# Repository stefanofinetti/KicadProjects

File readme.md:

# Kicad Projects File

This is a repository of my Kicad projects. Not everyone is working, I will list here the ones that I used and that I already sent to JLCPCB for printing.

* FCU_Mainboard_V3: a complete mainboard for FCU and both EFIS panels for Fenix A319/320/321. It is based on ATMega2560 chip with CH340G USB-To-Serial converter. All the components are SMD except for pin headers and the power selector switch to change between USB power and Bootloading using another card as Programmer. It works with Elral/Gagaru custom device firmare for Mobiflight since it has 6 SSD1306 OLED displays
* RMP_V2: a Radio Management Panel using ATMega2560 using two small OLED (0.96"), basically half the height of an SSD1306 OLED. It has a 9548APW chip and a separate 5V line for backlighting. It is meant to be mounted directly behind a 3d printed panel and provides backlighting to buttons and writings.
* LTS_Spooler: not Mobiflight related, it's the circuit board usable inside the fantastic LTS_Spooler project you can find here: https://makerworld.com/en/models/448008#profileId-354782

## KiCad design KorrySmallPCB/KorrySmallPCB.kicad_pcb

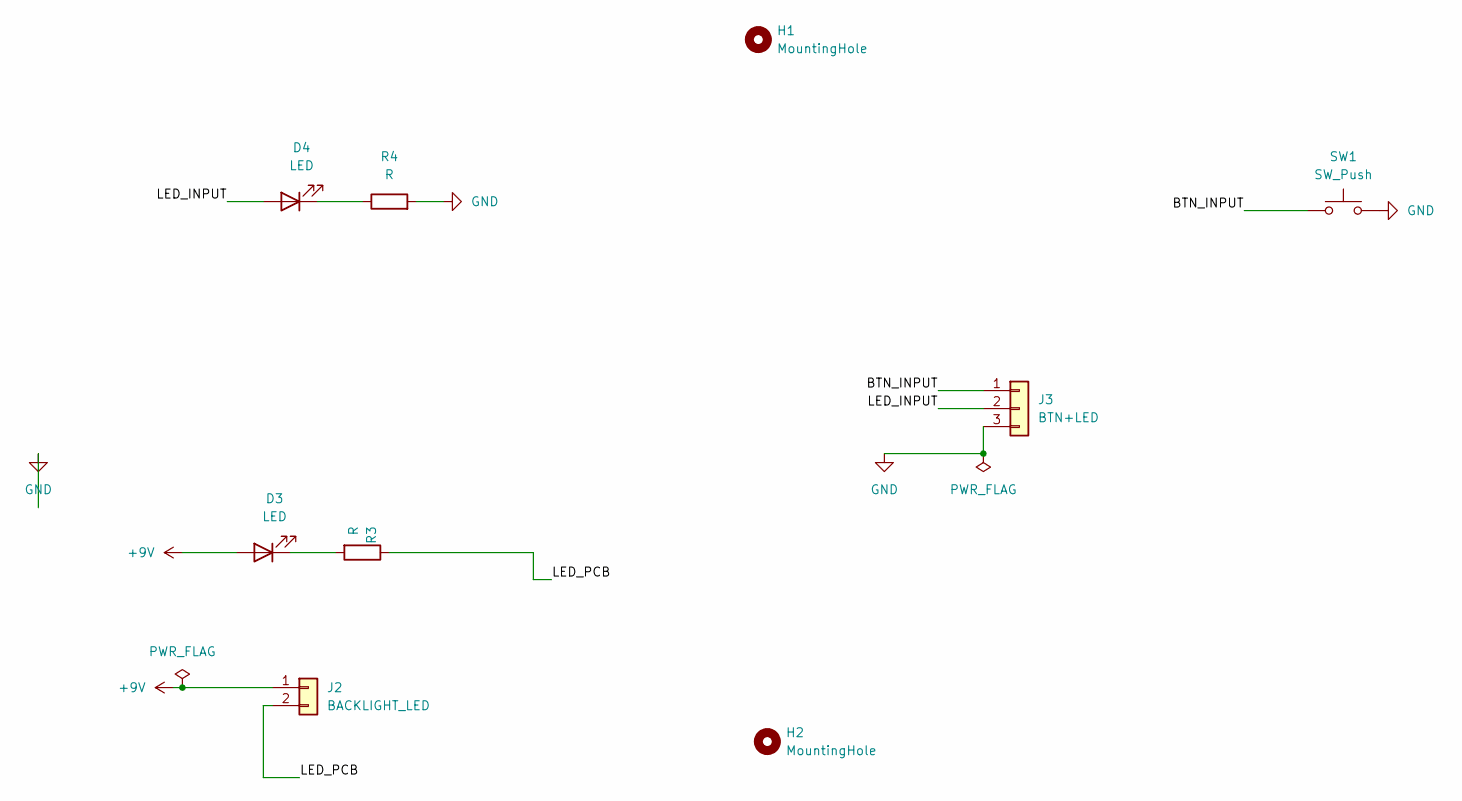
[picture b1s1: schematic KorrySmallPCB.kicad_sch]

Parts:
D3, D4: LED; LED_D3.0mm
H1, H2: MountingHole; MountingHole_2.2mm_M2_DIN965_Pad_TopBottom
J2: BACKLIGHT_LED; JST_EH_B2B-EH-A_1x02_P2.50mm_Vertical
J3: BTN+LED; JST_EH_B3B-EH-A_1x03_P2.50mm_Vertical
R3, R4: R; R_Axial_DIN0207_L6.3mm_D2.5mm_P7.62mm_Horizontal
SW1: SW_Push; SW_PUSH_1P1T_6x3.5mm_H4.3_APEM_MJTP1243

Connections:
+9V: D3.2 (A), J2.1
/BTN_INPUT: J3.1, SW1.1
/LED_INPUT: D4.2 (A), J3.2
/LED_PCB: J2.2, R3.1
GND: J3.3, R4.2, SW1.2
unnamed: D3.1 (K), R3.2
unnamed: D4.1 (K), R4.1

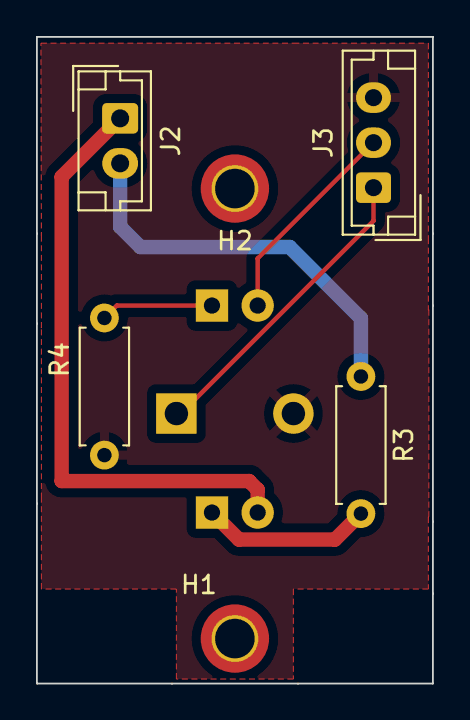
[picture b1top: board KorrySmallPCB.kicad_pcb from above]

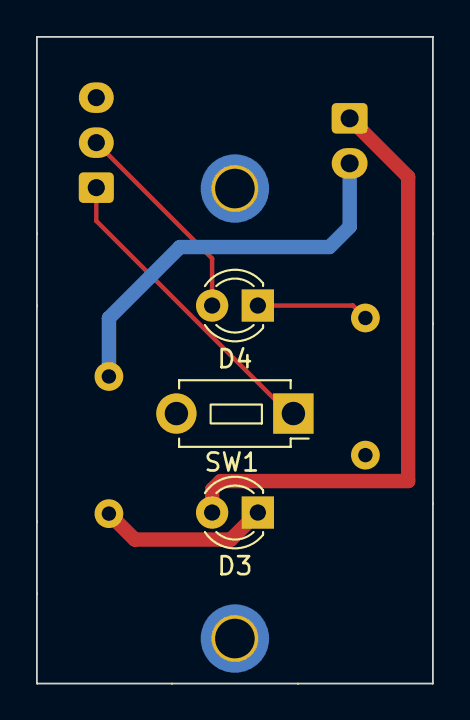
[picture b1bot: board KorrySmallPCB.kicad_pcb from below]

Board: 2 copper layers, 22.0 x 35.9 mm, 9 parts (3 on the bottom side), 7 nets.

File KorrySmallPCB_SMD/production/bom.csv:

Designator,Footprint,Quantity,Value,LCSC Part #
"DG-1, DW-1",1206,2,LED,
"H1, H2",MountingHole_2.5mm_Pad_TopBottom,2,MountingHole,
J1,PinHeader_1x03_P2.54mm_Vertical,1,BTN+LED,
J2,PinHeader_1x02_P2.54mm_Vertical,1,BK_LED,
"RG-1, RW-1",1206,2,R,
SW1,SW_PUSH_1P1T_6x3.5mm_H4.3_APEM_MJTP1243,1,SW,C4364985

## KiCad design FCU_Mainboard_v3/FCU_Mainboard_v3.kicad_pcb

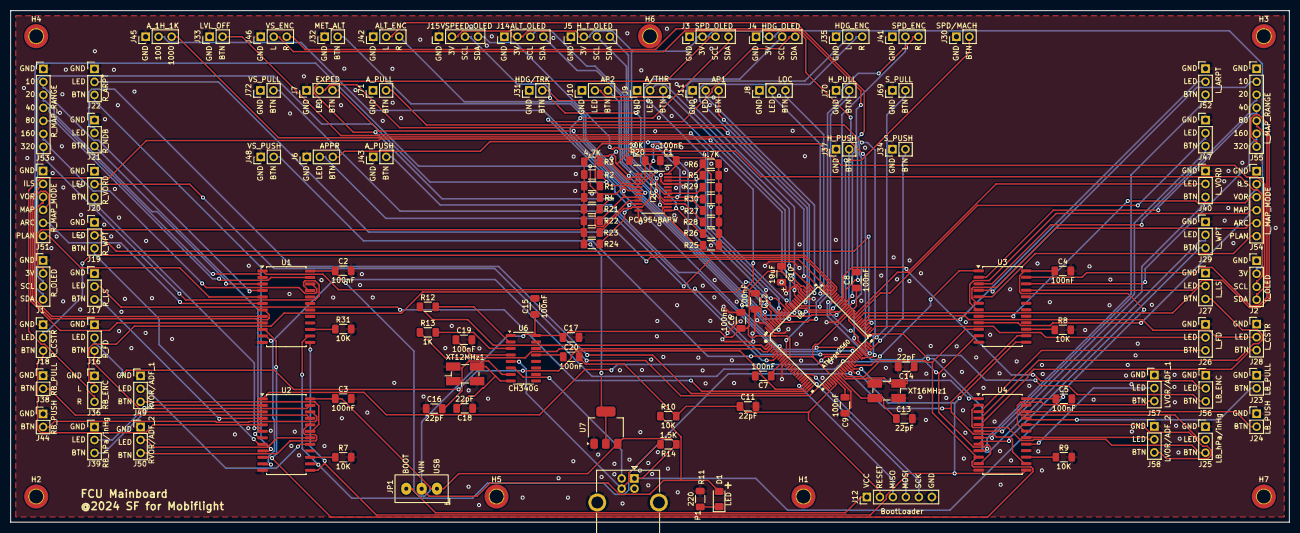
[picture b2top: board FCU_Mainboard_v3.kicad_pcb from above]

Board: 2 copper layers, 250.0 x 100.0 mm, 127 parts (0 on the bottom side), 156 nets.

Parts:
C1, C2, C3, C4, C5, C6, C7, C8, C9, C12, C15, C17, C19, C20: 100nF; C_1206_3216Metric_Pad1.33x1.80mm_HandSolder
C10: 10uF; C_1206_3216Metric_Pad1.33x1.80mm_HandSolder
C11, C13, C14, C16, C18: 22pF; C_1206_3216Metric_Pad1.33x1.80mm_HandSolder
D1: LED; LED_1206_3216Metric_Pad1.42x1.75mm_HandSolder
H1, H2, H3, H4, H5, H6, H7: MountingHole; MountingHole_2.7mm_M2.5_DIN965_Pad_TopBottom
I2C_1: PCA9548APW; SOP65P640X120-24N
J1: R_OLED; PinHeader_1x04_P2.54mm_Vertical
J2: L_OLED; PinHeader_1x04_P2.54mm_Vertical
J3: SPD_OLED; PinHeader_1x04_P2.54mm_Vertical
J4: HDG_OLED; PinHeader_1x04_P2.54mm_Vertical
J5: H_T_OLED; PinHeader_1x04_P2.54mm_Vertical
J6: APPR; PinHeader_1x03_P2.54mm_Vertical
J7: EXPED; PinHeader_1x03_P2.54mm_Vertical
J8: LOC; PinHeader_1x03_P2.54mm_Vertical
J9: A/THR; PinHeader_1x03_P2.54mm_Vertical
J10: AP2; PinHeader_1x03_P2.54mm_Vertical
J11: AP1; PinHeader_1x03_P2.54mm_Vertical
J12: BootLoader; PinHeader_1x06_P2.54mm_Vertical
J14: ALT_OLED; PinHeader_1x04_P2.54mm_Vertical
J15: VSPEED_OLED; PinHeader_1x04_P2.54mm_Vertical
J16: R_FD; PinHeader_1x03_P2.54mm_Vertical
J17: R_LS; PinHeader_1x03_P2.54mm_Vertical
J18: R_CSTR; PinHeader_1x03_P2.54mm_Vertical
J19: R_WPT; PinHeader_1x03_P2.54mm_Vertical
J20: R_VORD; PinHeader_1x03_P2.54mm_Vertical
J21: R_NDB; PinHeader_1x03_P2.54mm_Vertical
J22: R_ARPT; PinHeader_1x03_P2.54mm_Vertical
J23: LB_PULL; PinHeader_1x02_P2.54mm_Vertical
J24: LB_PUSH; PinHeader_1x02_P2.54mm_Vertical
J25: LB_hPa/inHg; PinHeader_1x03_P2.54mm_Vertical
J26: L_FD; PinHeader_1x03_P2.54mm_Vertical
J27: L_LS; PinHeader_1x03_P2.54mm_Vertical
J28: L_CSTR; PinHeader_1x03_P2.54mm_Vertical
J29: L_WPT; PinHeader_1x03_P2.54mm_Vertical
J30: SPD/MACH; PinHeader_1x02_P2.54mm_Vertical
J31: HDG/TRK; PinHeader_1x02_P2.54mm_Vertical
J32: MET_ALT; PinHeader_1x02_P2.54mm_Vertical
J33: LVL_OFF; PinHeader_1x02_P2.54mm_Vertical
J34: S_PUSH; PinHeader_1x02_P2.54mm_Vertical
J35: HDG_ENC; PinHeader_1x03_P2.54mm_Vertical
J36: RB_ENC; PinHeader_1x03_P2.54mm_Vertical
J37: H_PUSH; PinHeader_1x02_P2.54mm_Vertical
J38: RB_PULL; PinHeader_1x02_P2.54mm_Vertical
J39: RB_hPa/inHg; PinHeader_1x03_P2.54mm_Vertical
J40: L_VORD; PinHeader_1x03_P2.54mm_Vertical
J41: SPD_ENC; PinHeader_1x03_P2.54mm_Vertical
J42: ALT_ENC; PinHeader_1x03_P2.54mm_Vertical
J43: A_PUSH; PinHeader_1x02_P2.54mm_Vertical
J44: RB_PUSH; PinHeader_1x02_P2.54mm_Vertical
J45: A_1H_1K; PinHeader_1x03_P2.54mm_Vertical
J46: VS_ENC; PinHeader_1x03_P2.54mm_Vertical
J47: L_NDB; PinHeader_1x03_P2.54mm_Vertical
J48: VS_PUSH; PinHeader_1x02_P2.54mm_Vertical
J49: RVOR/ADF_1; PinHeader_1x03_P2.54mm_Vertical
J50: RVOR/ADF_2; PinHeader_1x03_P2.54mm_Vertical
J51: R_MAP_MODE; PinHeader_1x06_P2.54mm_Vertical
J52: L_ARPT; PinHeader_1x03_P2.54mm_Vertical
J53: R_MAP_RANGE; PinHeader_1x07_P2.54mm_Vertical
J54: L_MAP_MODE; PinHeader_1x06_P2.54mm_Vertical
J55: L_MAP_RANGE; PinHeader_1x07_P2.54mm_Vertical
J56: LB_ENC; PinHeader_1x03_P2.54mm_Vertical
J57: LVOR/ADF_1; PinHeader_1x03_P2.54mm_Vertical
J58: LVOR/ADF_2; PinHeader_1x03_P2.54mm_Vertical
J69: S_PULL; PinHeader_1x02_P2.54mm_Vertical
J70: H_PULL; PinHeader_1x02_P2.54mm_Vertical
J71: A_PULL; PinHeader_1x02_P2.54mm_Vertical
J72: VS_PULL; PinHeader_1x02_P2.54mm_Vertical
JP1: Power Selector; Slide_Switch_SPDT_P3mm_10x5x10mm
P1: USB_C_Plug_USB2.0; USB_B_OST_USB-B1HSxx_Horizontal
R1, R2, R3, R4, R5, R6, R21, R22, R23, R24, R25, R26, R27, R28, R29, R30: 4.7K; R_1206_3216Metric_Pad1.30x1.75mm_HandSolder
R7, R8, R9, R10, R20, R31: 10K; R_1206_3216Metric_Pad1.30x1.75mm_HandSolder
R11: 220; R_1206_3216Metric_Pad1.30x1.75mm_HandSolder
R12, R13: 1K; R_1206_3216Metric_Pad1.30x1.75mm_HandSolder
R14: 1.5K; R_1206_3216Metric_Pad1.30x1.75mm_HandSolder
U1, U2, U3, U4: CD74HC4067M; SOIC-24W_7.5x15.4mm_P1.27mm
U5: ATMega2560; TQFP100-0.5-14X14MM
U6: CH340G; SOIC-16_3.9x9.9mm_P1.27mm
U7: AMS1117-3.3; SOT-223-3_TabPin2
XT12MHz1: 12MHz; Crystal_SMD_EuroQuartz_MJ-4Pin_5.0x3.2mm_HandSoldering
XT16MHz1: 16MHz; Crystal_SMD_EuroQuartz_MJ-4Pin_5.0x3.2mm_HandSoldering

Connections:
+3V3: C1.1, I2C_1.24 (VCC), J1.2, J2.2, J3.2, J4.2, J5.2, J14.2, J15.2, R1.1, R2.2, R3.1, R4.1, R5.2, R6.1, R20.1, R21.1, R22.1, R23.1, R24.1, R25.1, R26.1, R27.1, R28.1, R29.1, R30.1, U7.2 (VO)
+5V: C2.1, C3.1, C4.1, C5.1, JP1.1 (A), P1.1 (VBUS), R14.1, U1.24 (VCC), U2.24 (VCC), U3.24 (VCC), U4.24 (VCC), U7.3 (VI)
/EFIS_LEFT/ADF 1: J57.3, U4.19 (I12)
/EFIS_LEFT/ADF 2: J58.3, U4.20 (I11)
/EFIS_LEFT/ARC: J54.5, U3.6 (I3)
/EFIS_LEFT/ARPT_BTN: J52.3, U4.9 (I0)
/EFIS_LEFT/BARO_PULL: J23.2, U4.21 (I10)
/EFIS_LEFT/BARO_PUSH: J24.2, U4.22 (I9)
/EFIS_LEFT/BARO_hPa: J25.2, U4.23 (I8)
/EFIS_LEFT/BARO_inHg: J25.3, U4.2 (I7)
/EFIS_LEFT/CSTR_BTN: J28.3, U4.5 (I4)
/EFIS_LEFT/FD_BTN: J26.3, U4.3 (I6)
/EFIS_LEFT/ILS: J54.2, U3.9 (I0)
/EFIS_LEFT/LS_BTN: J27.3, U4.4 (I5)
/EFIS_LEFT/MAP: J54.4, U3.7 (I2)
/EFIS_LEFT/NDB_BTN: J47.3, U4.7 (I2)
/EFIS_LEFT/PLAN: J54.6, U3.5 (I4)
/EFIS_LEFT/R10: J55.2, U3.4 (I5)
/EFIS_LEFT/R20: J55.3, U3.3 (I6)
/EFIS_LEFT/R40: J55.4, U3.2 (I7)
/EFIS_LEFT/R80: J55.5, U3.23 (I8)
/EFIS_LEFT/R160: J55.6, U3.22 (I9)
/EFIS_LEFT/R320: J55.7, U3.21 (I10)
/EFIS_LEFT/VOR: J54.3, U3.8 (I1)
/EFIS_LEFT/VOR 1: J57.2, U4.17 (I14)
/EFIS_LEFT/VOR 2: J58.2, U4.18 (I13)
/EFIS_LEFT/VORD_BTN: J40.3, U4.6 (I3)
/EFIS_LEFT/WPT_BTN: J29.3, U4.8 (I1)
/EFIS_RIGHT/ADF 1: J49.3, U2.19 (I12)
/EFIS_RIGHT/ADF 2: J50.3, U2.20 (I11)
/EFIS_RIGHT/ARC: J51.5, U1.6 (I3)
/EFIS_RIGHT/ARPT_BTN: J22.3, U2.9 (I0)
/EFIS_RIGHT/BARO_PULL: J38.2, U2.21 (I10)
/EFIS_RIGHT/BARO_PUSH: J44.2, U2.22 (I9)
/EFIS_RIGHT/BARO_hPa: J39.2, U2.23 (I8)
/EFIS_RIGHT/BARO_inHg: J39.3, U2.2 (I7)
/EFIS_RIGHT/CSTR_BTN: J18.3, U2.5 (I4)
/EFIS_RIGHT/FD_BTN: J16.3, U2.3 (I6)
/EFIS_RIGHT/ILS: J51.2, U1.9 (I0)
/EFIS_RIGHT/LS_BTN: J17.3, U2.4 (I5)
/EFIS_RIGHT/MAP: J51.4, U1.7 (I2)
/EFIS_RIGHT/NDB_BTN: J21.3, U2.7 (I2)
/EFIS_RIGHT/PLAN: J51.6, U1.5 (I4)
/EFIS_RIGHT/R10: J53.2, U1.4 (I5)
/EFIS_RIGHT/R20: J53.3, U1.3 (I6)
/EFIS_RIGHT/R40: J53.4, U1.2 (I7)
/EFIS_RIGHT/R80: J53.5, U1.23 (I8)
/EFIS_RIGHT/R160: J53.6, U1.22 (I9)
/EFIS_RIGHT/R320: J53.7, U1.21 (I10)
/EFIS_RIGHT/VOR: J51.3, U1.8 (I1)
/EFIS_RIGHT/VOR 1: J49.2, U2.17 (I14)
/EFIS_RIGHT/VOR 2: J50.2, U2.18 (I13)
/EFIS_RIGHT/VORD_BTN: J20.3, U2.6 (I3)
/EFIS_RIGHT/WPT_BTN: J19.3, U2.8 (I1)
/OLEDs/ALT_SCL: I2C_1.16 (SC5), J14.3, R27.2
/OLEDs/ALT_SDA: I2C_1.15 (SD5), J14.4, R28.2
/OLEDs/HDG_SCL: I2C_1.11 (SC3), J4.3, R23.2
/OLEDs/HDG_SDA: I2C_1.10 (SD3), J4.4, R24.2
/OLEDs/HDG/TRK_SCL: I2C_1.14 (SC4), J5.3, R25.2
/OLEDs/HDG/TRK_SDA: I2C_1.13 (SD4), J5.4, R26.2
/OLEDs/L_EFIS_SCL: I2C_1.7 (SC1), J2.3, R1.2
/OLEDs/L_EFIS_SDA: I2C_1.4 (SD0), J2.4, R3.2
/OLEDs/R_EFIS_SCL: I2C_1.5 (SC0), J1.3, R2.1
/OLEDs/R_EFIS_SDA: I2C_1.6 (SD1), J1.4, R4.2
/OLEDs/SPD_SCL: I2C_1.9 (SC2), J3.3, R21.2
/OLEDs/SPD_SDA: I2C_1.8 (SD2), J3.4, R22.2
/OLEDs/VSPEED_SCL: I2C_1.18 (SC6), J15.3, R29.2
/OLEDs/VSPEED_SDA: I2C_1.17 (SD6), J15.4, R30.2
ALT_100: J45.2, U5.45 (PD2)
ALT_1000: J45.3, U5.46 (PD3)
ALT_LEFT: J42.2, U5.63 (PJ0)
ALT_PULL: J71.2, U5.44 (PD1)
ALT_PUSH: J43.2, U5.43 (PD0)
ALT_RIGHT: J42.3, U5.64 (PJ1)
AP1_BTN: J11.3, U5.9 (PE7)
AP1_LED: J10.2, U5.78 (PA0)
AP2_BTN: J10.3, U5.97 (PF0)
AP2_LED: J11.2, U5.77 (PA1)
APPR_BTN: J6.3, U5.96 (PF1)
APPR_LED: J6.2, U5.75 (PA3)
A/THR_BTN: J9.3, U5.8 (PE6)
A/THR_LED: J9.2, U5.76 (PA2)
EXPED_BTN: J7.3, U5.95 (PF2)
EXPED_LED: J7.2, U5.74 (PA4)
GND: C1.2, C2.2, C3.2, C4.2, C5.2, C6.2, C7.2, C8.2, C9.2, C10.2, C11.2, C12.2, C13.2, C14.2, C15.2, C16.1, C17.2, C18.1, C19.2, I2C_1.1 (A0), I2C_1.2 (A1), I2C_1.12 (GND), I2C_1.21 (A2), J1.1, J2.1, J3.1, J4.1, J5.1, J6.1, J7.1, J8.1, J9.1, J10.1, J11.1, J12.6, J14.1, J15.1, J16.1, J17.1, J18.1, J19.1, J20.1, J21.1, J22.1, J23.1, J24.1, J25.1, J26.1, J27.1, J28.1, J29.1, J30.1, J31.1, J32.1, J33.1, J34.1, J35.1, J36.1, J37.1, J38.1, J39.1, J40.1, J41.1, J42.1, J43.1, J44.1, J45.1, J46.1, J47.1, J48.1, J49.1, J50.1, J51.1, J52.1, J53.1, J54.1, J55.1, J56.1, J57.1, J58.1, J69.1, J70.1, J71.1, J72.1, P1.4 (GND), P1.5 (Shield), R7.2, R8.2, R9.2, R11.1, R31.2, U1.12 (GND), U2.12 (GND), U3.12 (GND), U4.12 (GND), U5.11 (GND), U5.32 (GND), U5.62 (GND), U5.81 (GND), U5.99 (GND), U6.1 (GND), U7.1 (GND), XT12MHz1.2, XT12MHz1.4, XT16MHz1.2, XT16MHz1.4
HDG_LEFT: J35.2, U5.83 (PK6)
HDG_PULL: J70.2, U5.48 (PD5)
HDG_PUSH: J37.2, U5.47 (PD4)
HDG_RIGHT: J35.3, U5.82 (PK7)
HDG/TRK_BTN: J31.2, U5.93 (PF4)
LOC_BTN: J8.3, U5.94 (PF3)
LOC_LED: J8.2, U5.73 (PA5)
LVL_OFF_BTN: J33.2, U5.92 (PF5)
L_EFIS_ARPT_LED: J52.2, U5.54 (PC1)
L_EFIS_BARO_LEFT: J56.2, U5.67 (PJ4)
L_EFIS_BARO_RIGHT: J56.3, U5.68 (PJ5)
L_EFIS_CSTR_LED: J28.2, U5.55 (PC2)
L_EFIS_FD_LED: J26.2, U5.56 (PC3)
L_EFIS_LS_LED: J27.2, U5.57 (PC4)
L_EFIS_NDB_LED: J47.2, U5.58 (PC5)
L_EFIS_VORD_LED: J40.2, U5.59 (PC6)
L_EFIS_WPT_LED: J29.2, U5.60 (PC7)
METRIC_ALT_BTN: J32.2, U5.91 (PF6)
MISO: J12.3, U5.22 (PB3)
MOSI: J12.4, U5.21 (PB2)
MP_S0: U1.10 (S0), U2.10 (S0), U3.10 (S0), U4.10 (S0), U5.35 (PL0)
MP_S1: U1.11 (S1), U2.11 (S1), U3.11 (S1), U4.11 (S1), U5.36 (PL1)
MP_S2: U1.14 (S2), U2.14 (S2), U3.14 (S2), U4.14 (S2), U5.37 (PL2)
MP_S3: U1.13 (S3), U2.13 (S3), U3.13 (S3), U4.13 (S3), U5.38 (PL3)
unnamed: D1.1 (K), R11.2
unnamed: I2C_1.3 (~RESET), R20.2
unnamed: R31.1, U1.15 (~E)
unnamed: R7.1, U2.15 (~E)
unnamed: R8.1, U3.15 (~E)
unnamed: R9.1, U4.15 (~E)
unnamed: C12.1, U5.98 (AREF)
unnamed: C14.1, U5.34 (XTAL1), XT16MHz1.1
unnamed: C13.1, U5.33 (XTAL2), XT16MHz1.3
unnamed: R13.2, U6.3 (RXD)
unnamed: R12.2, U6.2 (TXD)
unnamed: C19.1, U6.4 (V3)
unnamed: C16.2, U6.7 (XI), XT12MHz1.1
unnamed: C18.2, U6.8 (XO), XT12MHz1.3
unnamed: C20.1, U6.13 (~DTR)
RESET: C11.1, C20.2, J12.2, R10.2, U5.30 (~RESET)
RXD: R12.1, U5.2 (PE0)
R_EFIS_ARPT_LED: J22.2, U5.72 (PA6)
R_EFIS_BARO_LEFT: J36.2, U5.87 (PK2)
R_EFIS_BARO_RIGHT: J36.3, U5.86 (PK3)
R_EFIS_CSTR_LED: J18.2, U5.71 (PA7)
R_EFIS_FD_LED: J16.2, U5.23 (PB4)
R_EFIS_LS_LED: J17.2, U5.24 (PB5)
R_EFIS_NDB_LED: J21.2, U5.25 (PB6)
R_EFIS_VORD_LED: J20.2, U5.26 (PB7)
R_EFIS_WPT_LED: J19.2, U5.53 (PC0)
SCK: J12.5, U5.20 (PB1)
SCL: I2C_1.22 (SCL), R5.1, U5.89 (PK0)
SDA: I2C_1.23 (SDA), R6.2, U5.88 (PK1)
SPD_LEFT: J41.2, U5.85 (PK4)
SPD_PULL: J69.2, U5.50 (PD7)
SPD_PUSH: J34.2, U5.49 (PD6)
SPD_RIGHT: J41.3, U5.84 (PK5)
SPD/MACH_BTN: J30.2, U5.90 (PF7)
TXD: R13.1, U5.3 (PE1)
U1_MP_SIG: U1.1 (COM), U5.42 (PL7)
U2_MP_SIG: U2.1 (COM), U5.41 (PL6)
U3_MP_SIG: U3.1 (COM), U5.40 (PL5)
U4_MP_SIG: U4.1 (COM), U5.39 (PL4)
UD+: P1.3 (D+), R14.2, U6.5 (UD+)
UD-: P1.2 (D-), U6.6 (UD-)
VCC: J12.1, JP1.3 (C)
VIN: C6.1, C7.1, C8.1, C9.1, C10.1, C15.1, C17.1, D1.2 (A), JP1.2 (B), R10.1, U5.10 (VCC), U5.31 (VCC), U5.61 (VCC), U5.80 (VCC), U5.100 (AVCC), U6.16 (VCC)
VSPEED_LEFT: J46.2, U5.65 (PJ2)
VSPEED_PULL: J72.2, U5.7 (PE5)
VSPEED_PUSH: J48.2, U5.6 (PE4)
VSPEED_RIGHT: J46.3, U5.66 (PJ3)

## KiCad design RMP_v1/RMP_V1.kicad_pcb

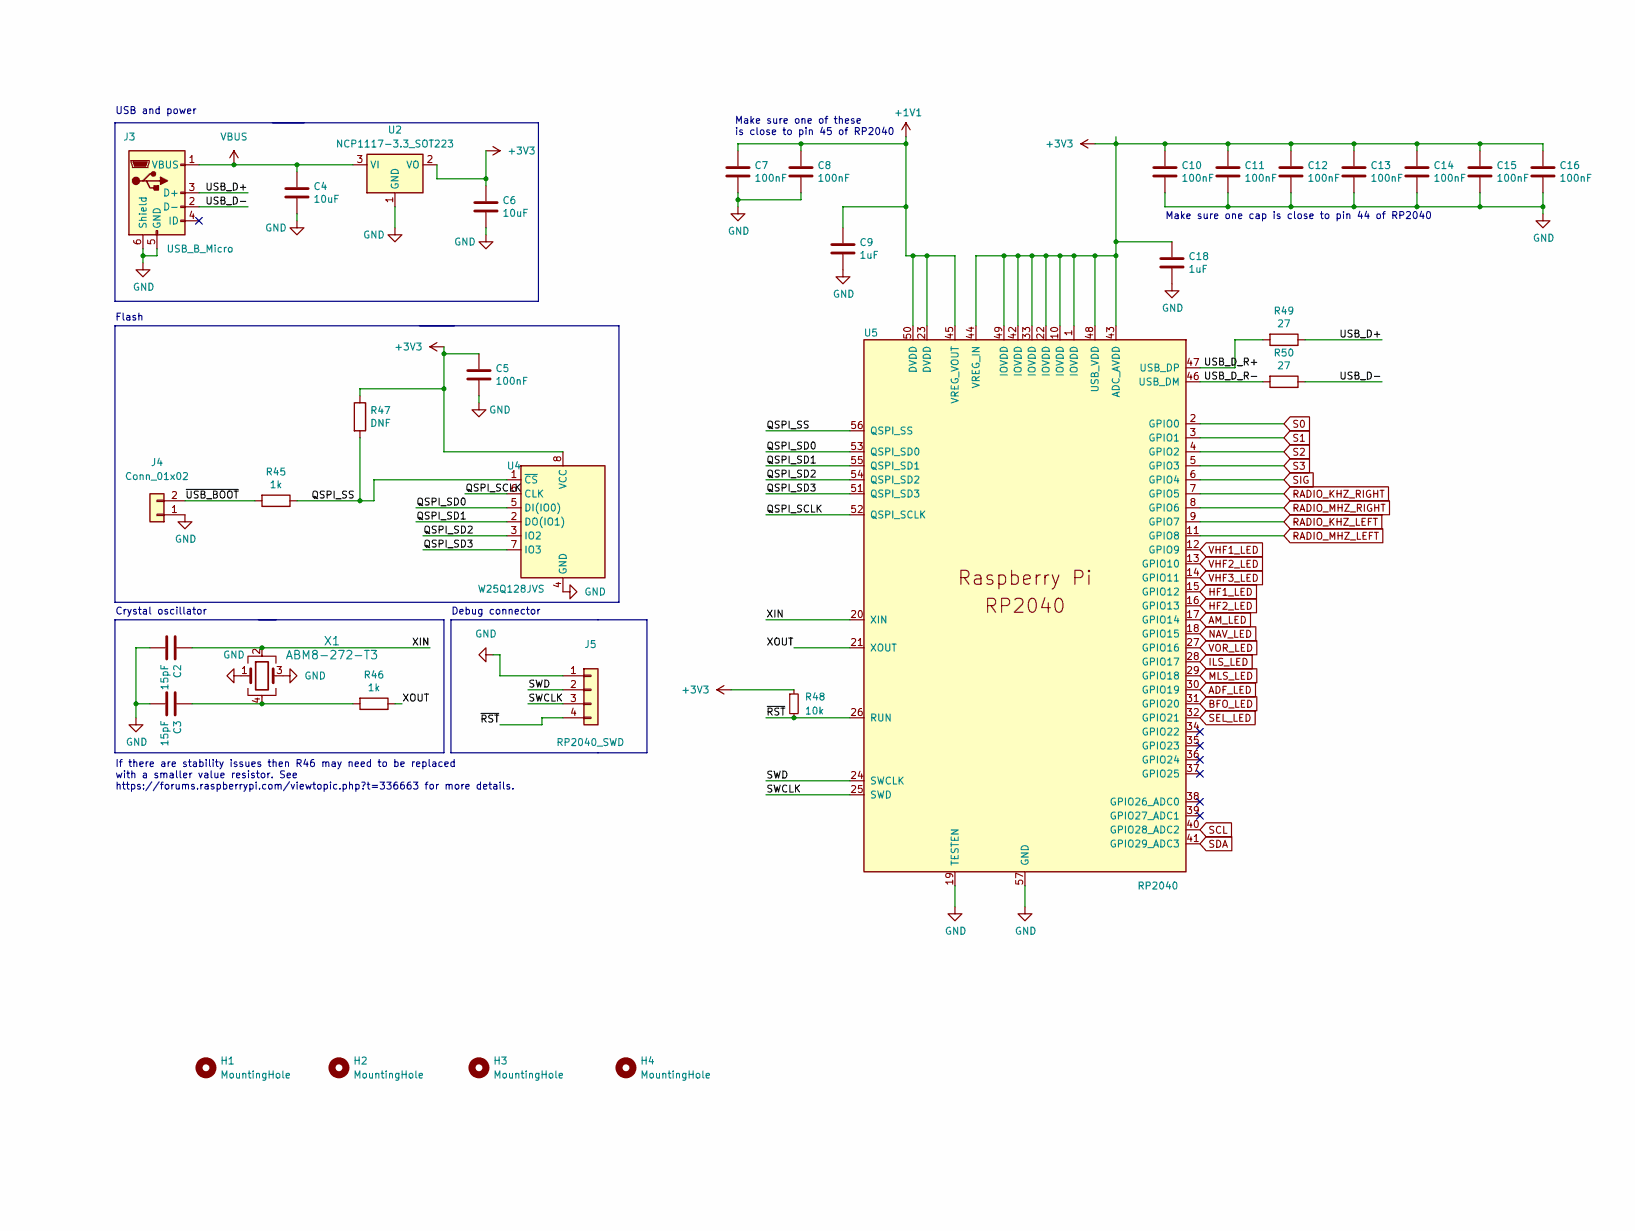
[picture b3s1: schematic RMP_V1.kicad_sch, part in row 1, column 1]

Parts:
C2, C3: 15pF; Perfect_0402; MPN - JLCPCB C32949
C4, C6: 10uF; Perfect_0402; MPN - JLCPCB C52923
C5, C7, C8, C10, C11, C12, C13, C14, C15, C16: 100nF; Perfect_0402; MPN - JLCPCB C52923
C9, C18: 1uF; Perfect_0402; MPN - JLCPCB C52923
H1, H2, H3, H4: MountingHole; MountingHole_3.2mm_M3
J3: USB_B_Micro; USB_B_Mini_Amphenol_UE25BE5510H
J4: Conn_01x02; PinHeader_1x02_P2.54mm_Vertical
J5: RP2040_SWD; PinHeader_1x04_P2.54mm_Vertical
R45, R46: 1k; R_0402_1005Metric; MPN - JLCPCB C11702
R47: DNF; R_0402_1005Metric
R48: 10k; R_0402_1005Metric; MPN - JLCPCB C25744
R49, R50: 27; R_0402_1005Metric; MPN - JLCPCB C25190
U2: NCP1117-3.3_SOT223; SOT-223-3_TabPin2; MPN - JLCPCB C6186
U4: W25Q128JVS; SOIC-8_5.23x5.23mm_P1.27mm; MPN - JLCPCB C97521
U5: RP2040; QFN-56-1EP_7x7mm_P0.4mm_EP3.2x3.2mm; MPN - JLCPCB C2040
X1: ABM8-272-T3; Crystal_SMD_3225-4Pin_3.2x2.5mm; MPN - JLCPCB C9002

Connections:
+1V1: C7.1, C8.1, C9.1, U5.23 (DVDD), U5.45 (VREG_VOUT), U5.50 (DVDD)
+3V3: C5.1, C6.1, C10.1, C11.1, C12.1, C13.1, C14.1, C15.1, C16.1, C18.1, R47.1, R48.1, U2.2 (VO), U4.8 (VCC), U5.1 (IOVDD), U5.10 (IOVDD), U5.22 (IOVDD), U5.33 (IOVDD), U5.42 (IOVDD), U5.43 (ADC_AVDD), U5.44 (VREG_IN), U5.48 (USB_VDD), U5.49 (IOVDD); also elsewhere on the board
/QSPI_SCLK: U4.6 (CLK), U5.52 (QSPI_SCLK)
/QSPI_SD0: U4.5 (DI(IO0)), U5.53 (QSPI_SD0)
/QSPI_SD1: U4.2 (DO(IO1)), U5.55 (QSPI_SD1)
/QSPI_SD2: U4.3 (IO2), U5.54 (QSPI_SD2)
/QSPI_SD3: U4.7 (IO3), U5.51 (QSPI_SD3)
/QSPI_SS: R45.1, R47.2, U4.1 (~CS), U5.56 (QSPI_SS)
/SWCLK: J5.3, U5.25 (SWD)
/SWD: J5.2, U5.24 (SWCLK)
/USB_D+: J3.3 (D+), R49.1
/USB_D-: J3.2 (D-), R50.1
/USB_D_R+: R49.2, U5.47 (USB_DP)
/USB_D_R-: R50.2, U5.46 (USB_DM)
/XIN: C2.1, U5.20 (XIN), X1.2
/XOUT: R46.1, U5.21 (XOUT)
/~RST: J5.4, R48.2, U5.26 (RUN)
/~USB_BOOT: J4.2, R45.2
ADF_LED: U5.30 (GPIO19); also elsewhere on the board
AM_LED: U5.17 (GPIO14); also elsewhere on the board
BFO_LED: U5.31 (GPIO20); also elsewhere on the board
GND: C2.2, C3.2, C4.2, C5.2, C6.2, C7.2, C8.2, C9.2, C10.2, C11.2, C12.2, C13.2, C14.2, C15.2, C16.2, C18.2, J3.5 (GND), J3.6 (Shield), J4.1, J5.1, U2.1 (GND), U4.4 (GND), U5.19 (TESTEN), U5.57 (GND), X1.1, X1.3; also elsewhere on the board
HF1_LED: U5.15 (GPIO12); also elsewhere on the board
HF2_LED: U5.16 (GPIO13); also elsewhere on the board
ILS_LED: U5.28 (GPIO17); also elsewhere on the board
MLS_LED: U5.29 (GPIO18); also elsewhere on the board
NAV_LED: U5.18 (GPIO15); also elsewhere on the board
unnamed: C3.1, R46.2, X1.4
RADIO_KHZ_LEFT: U5.9 (GPIO7); also elsewhere on the board
RADIO_KHZ_RIGHT: U5.7 (GPIO5); also elsewhere on the board
RADIO_MHZ_LEFT: U5.11 (GPIO8); also elsewhere on the board
RADIO_MHZ_RIGHT: U5.8 (GPIO6); also elsewhere on the board
S0: U5.2 (GPIO0); also elsewhere on the board
S1: U5.3 (GPIO1); also elsewhere on the board
S2: U5.4 (GPIO2); also elsewhere on the board
S3: U5.5 (GPIO3); also elsewhere on the board
SCL: U5.40 (GPIO28_ADC2); also elsewhere on the board
SDA: U5.41 (GPIO29_ADC3); also elsewhere on the board
SEL_LED: U5.32 (GPIO21); also elsewhere on the board
SIG: U5.6 (GPIO4); also elsewhere on the board
VBUS: C4.1, J3.1 (VBUS), U2.3 (VI); also elsewhere on the board
VHF1_LED: U5.12 (GPIO9); also elsewhere on the board
VHF2_LED: U5.13 (GPIO10); also elsewhere on the board
VHF3_LED: U5.14 (GPIO11); also elsewhere on the board
VOR_LED: U5.27 (GPIO16); also elsewhere on the board

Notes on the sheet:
Make sure one cap is close to pin 44 of RP2040
Crystal oscillator
USB and power
Make sure one of these is close to pin 45 of RP2040
Flash
If there are stability issues then R46 may need to be replaced with a smaller value resistor. See https://forums.raspberrypi.com/viewtopic.php?t=336663 for more details.
Debug connector

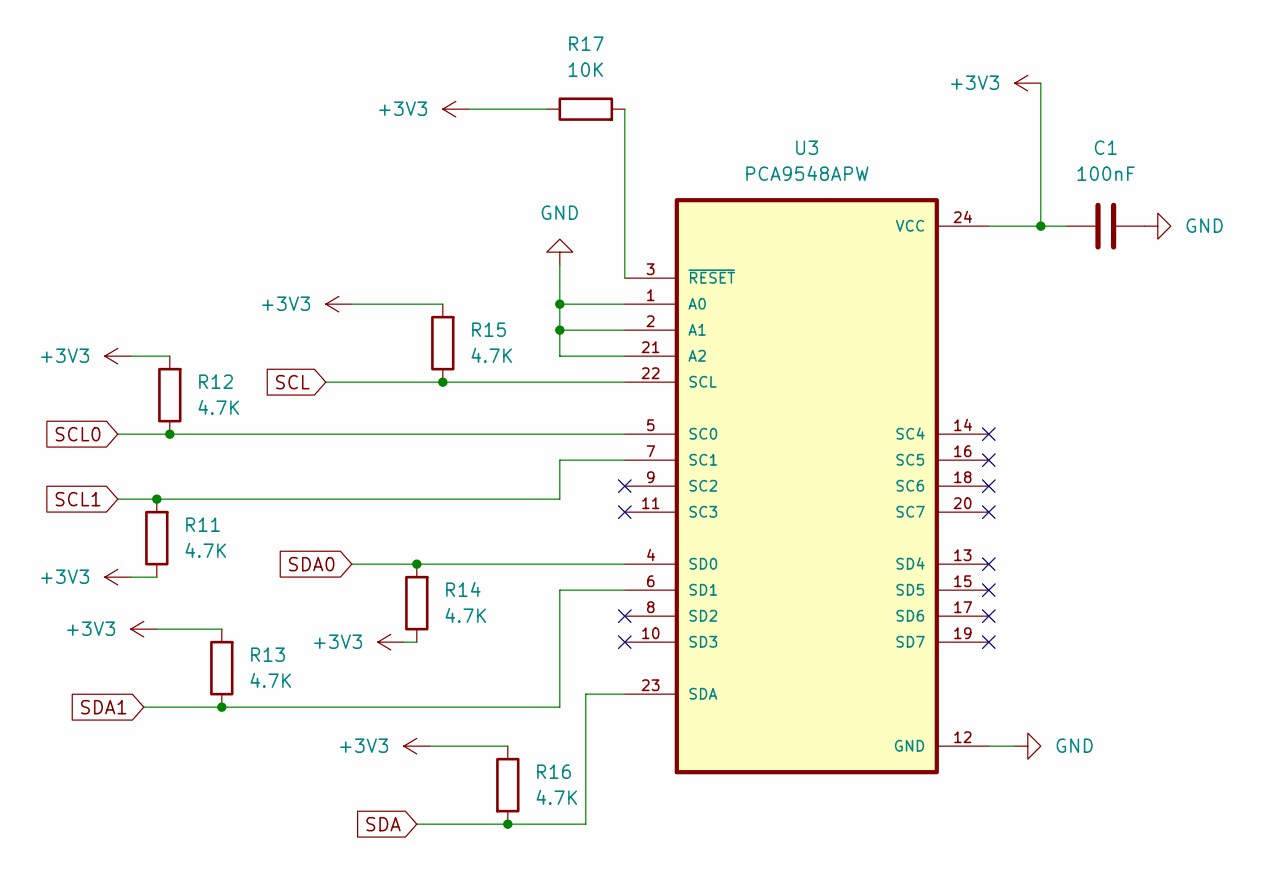
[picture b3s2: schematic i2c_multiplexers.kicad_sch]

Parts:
C1: 100nF; Perfect_0402
R11, R12, R13, R14, R15, R16: 4.7K; R_0402_1005Metric
R17: 10K; R_0402_1005Metric
U3: PCA9548APW; SOP65P640X120-24N

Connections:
+3V3: C1.1, R11.1, R12.2, R13.2, R14.1, R15.2, R16.1, R17.1, U3.24 (VCC); also elsewhere on the board
GND: C1.2, U3.1 (A0), U3.2 (A1), U3.12 (GND), U3.21 (A2); also elsewhere on the board
unnamed: R17.2, U3.3 (~RESET)
SCL: R15.1, U3.22 (SCL); also elsewhere on the board
SCL0: R12.1, U3.5 (SC0); also elsewhere on the board
SCL1: R11.2, U3.7 (SC1); also elsewhere on the board
SDA: R16.2, U3.23 (SDA); also elsewhere on the board
SDA0: R14.2, U3.4 (SD0); also elsewhere on the board
SDA1: R13.1, U3.6 (SD1); also elsewhere on the board

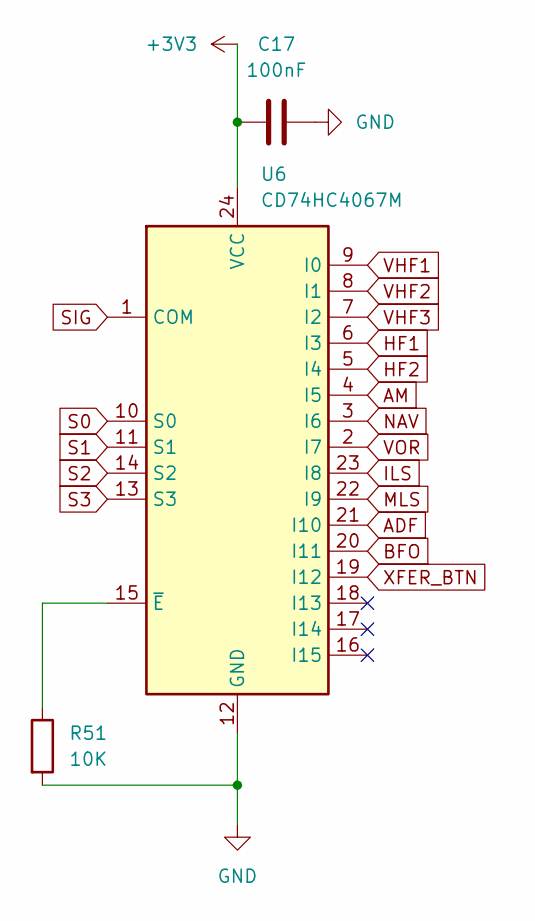
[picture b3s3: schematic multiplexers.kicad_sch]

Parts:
C17: 100nF; Perfect_0402
R51: 10K; R_0402_1005Metric
U6: CD74HC4067M; SOIC-24W_7.5x15.4mm_P1.27mm

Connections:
+3V3: C17.1, U6.24 (VCC); also elsewhere on the board
ADF: U6.21 (I10); also elsewhere on the board
AM: U6.4 (I5); also elsewhere on the board
BFO: U6.20 (I11); also elsewhere on the board
GND: C17.2, R51.2, U6.12 (GND); also elsewhere on the board
HF1: U6.6 (I3); also elsewhere on the board
HF2: U6.5 (I4); also elsewhere on the board
ILS: U6.23 (I8); also elsewhere on the board
MLS: U6.22 (I9); also elsewhere on the board
NAV: U6.3 (I6); also elsewhere on the board
unnamed: R51.1, U6.15 (~E)
S0: U6.10 (S0); also elsewhere on the board
S1: U6.11 (S1); also elsewhere on the board
S2: U6.14 (S2); also elsewhere on the board
S3: U6.13 (S3); also elsewhere on the board
SIG: U6.1 (COM); also elsewhere on the board
VHF1: U6.9 (I0); also elsewhere on the board
VHF2: U6.8 (I1); also elsewhere on the board
VHF3: U6.7 (I2); also elsewhere on the board
VOR: U6.2 (I7); also elsewhere on the board
XFER_BTN: U6.19 (I12); also elsewhere on the board

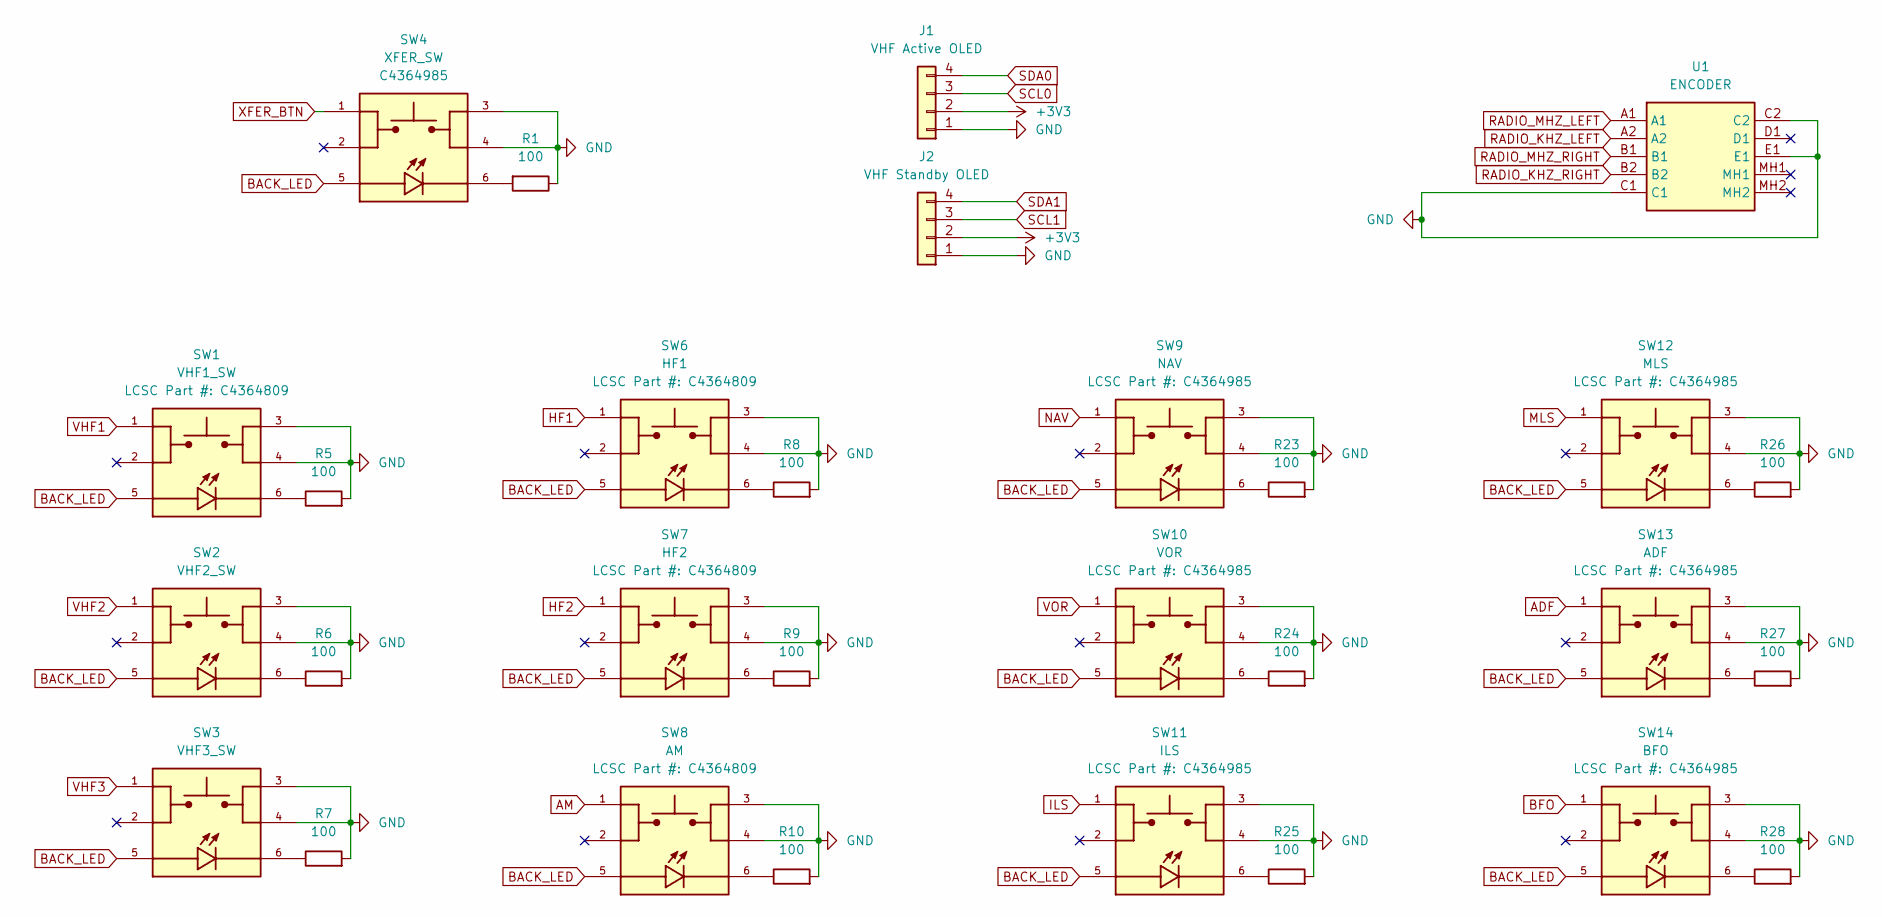
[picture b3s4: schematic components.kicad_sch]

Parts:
J1: VHF Active OLED; PinSocket_1x04_P2.54mm_Vertical
J2: VHF Standby OLED; PinSocket_1x04_P2.54mm_Vertical
R1, R5, R6, R7, R8, R9, R10, R23, R24, R25, R26, R27, R28: 100; R_0402_1005Metric
SW1: VHF1_SW; SW_TL3240F260R; PARTREV D; LCSC Part # C4364809
SW2: VHF2_SW; SW_TL3240F260R; PARTREV D; LCSC Part # C4364809
SW3: VHF3_SW; SW_TL3240F260R; PARTREV D; LCSC Part # C4364809
SW4: XFER_SW; SW_TL3240F260R; PARTREV D; LCSC Part # C4364985
SW6: HF1; SW_TL3240F260R; PARTREV D; LCSC Part # C4364809
SW7: HF2; SW_TL3240F260R; PARTREV D; LCSC Part # C4364809
SW8: AM; SW_TL3240F260R; PARTREV D; LCSC Part # C4364809
SW9: NAV; SW_TL3240F260R; PARTREV D; LCSC Part # C4364985
SW10: VOR; SW_TL3240F260R; PARTREV D; LCSC Part # C4364985
SW11: ILS; SW_TL3240F260R; PARTREV D; LCSC Part # C4364985
SW12: MLS; SW_TL3240F260R; PARTREV D; LCSC Part # C4364985
SW13: ADF; SW_TL3240F260R; PARTREV D; LCSC Part # C4364985
SW14: BFO; SW_TL3240F260R; PARTREV D; LCSC Part # C4364985
U1: ENCODER; EC11EBB24C03; Manufacturer_Part_Number EC11EBB24C03; Mouser Part Number 688-EC11EBB24C03

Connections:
+3V3: J1.2, J2.2; also elsewhere on the board
ADF: SW13.1; also elsewhere on the board
AM: SW8.1; also elsewhere on the board
BACK_LED: SW1.5, SW2.5, SW3.5, SW4.5, SW6.5, SW7.5, SW8.5, SW9.5, SW10.5, SW11.5, SW12.5, SW13.5, SW14.5
BFO: SW14.1; also elsewhere on the board
GND: J1.1, J2.1, R1.1, R5.2, R6.2, R7.2, R8.2, R9.2, R10.2, R23.2, R24.2, R25.2, R26.2, R27.2, R28.2, SW1.3, SW1.4, SW2.3, SW2.4, SW3.3, SW3.4, SW4.3, SW4.4, SW6.3, SW6.4, SW7.3, SW7.4, SW8.3, SW8.4, SW9.3, SW9.4, SW10.3, SW10.4, SW11.3, SW11.4, SW12.3, SW12.4, SW13.3, SW13.4, SW14.3, SW14.4, U1.C1, U1.C2, U1.E1; also elsewhere on the board
HF1: SW6.1; also elsewhere on the board
HF2: SW7.1; also elsewhere on the board
ILS: SW11.1; also elsewhere on the board
MLS: SW12.1; also elsewhere on the board
NAV: SW9.1; also elsewhere on the board
unnamed: R1.2, SW4.6
unnamed: R5.1, SW1.6
unnamed: R6.1, SW2.6
unnamed: R7.1, SW3.6
unnamed: R8.1, SW6.6
unnamed: R9.1, SW7.6
unnamed: R10.1, SW8.6
unnamed: R23.1, SW9.6
unnamed: R24.1, SW10.6
unnamed: R25.1, SW11.6
unnamed: R26.1, SW12.6
unnamed: R27.1, SW13.6
unnamed: R28.1, SW14.6
RADIO_KHZ_LEFT: U1.A2; also elsewhere on the board
RADIO_KHZ_RIGHT: U1.B2; also elsewhere on the board
RADIO_MHZ_LEFT: U1.A1; also elsewhere on the board
RADIO_MHZ_RIGHT: U1.B1; also elsewhere on the board
SCL0: J1.3; also elsewhere on the board
SCL1: J2.3; also elsewhere on the board
SDA0: J1.4; also elsewhere on the board
SDA1: J2.4; also elsewhere on the board
VHF1: SW1.1; also elsewhere on the board
VHF2: SW2.1; also elsewhere on the board
VHF3: SW3.1; also elsewhere on the board
VOR: SW10.1; also elsewhere on the board
XFER_BTN: SW4.1; also elsewhere on the board
